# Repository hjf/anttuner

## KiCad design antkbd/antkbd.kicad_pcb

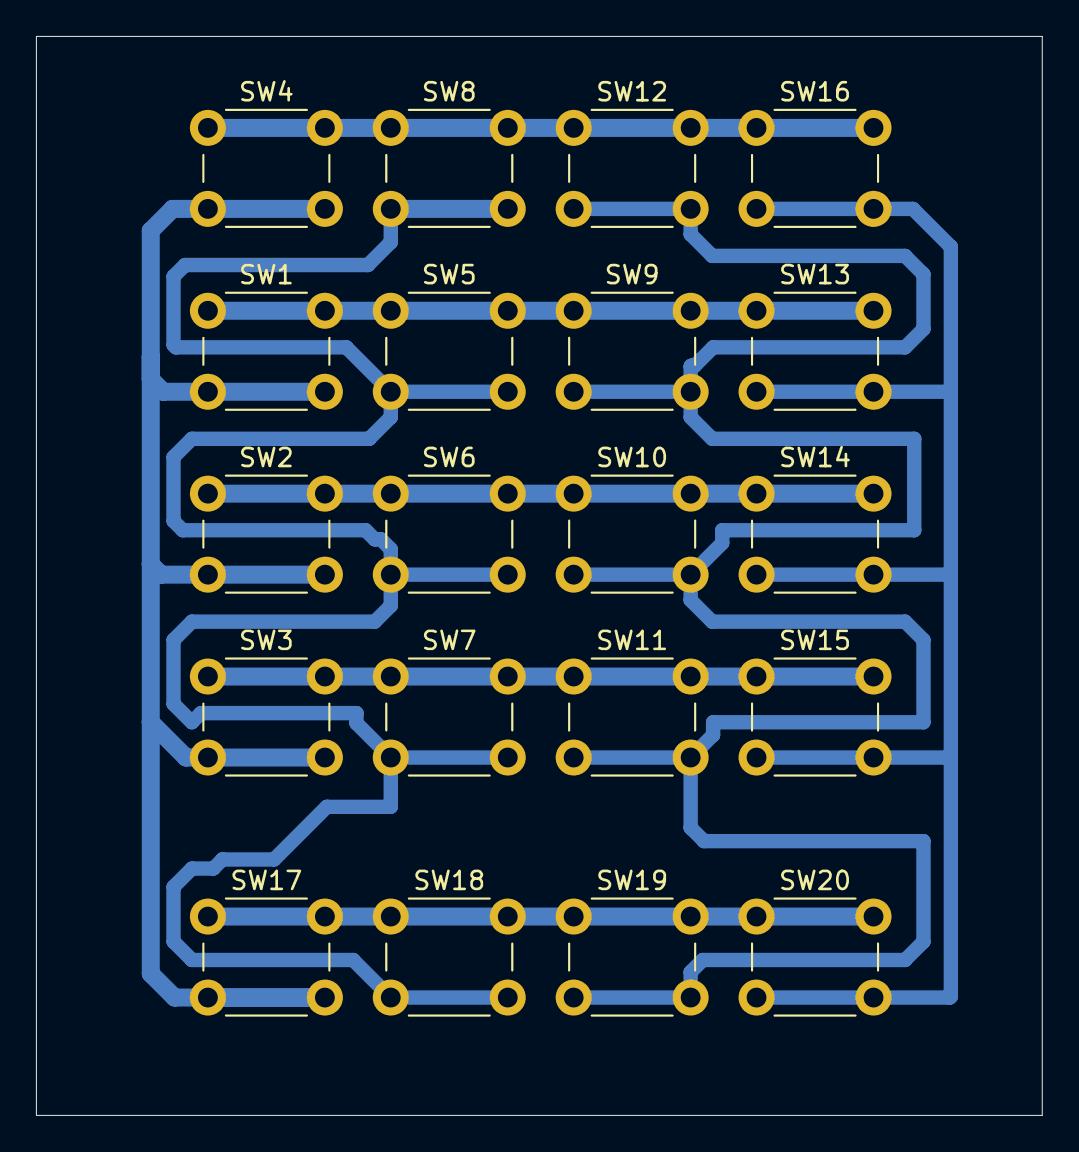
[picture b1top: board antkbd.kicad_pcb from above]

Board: 2 copper layers, 55.9 x 59.9 mm, 20 parts (0 on the bottom side), 9 nets.

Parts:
SW1, SW2, SW3, SW4, SW5, SW6, SW7, SW8, SW9, SW10, SW11, SW12, SW13, SW14, SW15, SW16, SW17, SW18, SW19, SW20: SW_Push_45deg; SW_PUSH_6mm

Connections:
unnamed: SW1.1, SW5.1, SW9.1, SW13.1
unnamed: SW1.2, SW2.2, SW3.2, SW4.2, SW17.2
unnamed: SW2.1, SW6.1, SW10.1, SW14.1
unnamed: SW9.2, SW10.2, SW11.2, SW12.2, SW19.2
unnamed: SW3.1, SW7.1, SW11.1, SW15.1
unnamed: SW4.1, SW8.1, SW12.1, SW16.1
unnamed: SW13.2, SW14.2, SW15.2, SW16.2, SW20.2
unnamed: SW17.1, SW18.1, SW19.1, SW20.1
unnamed: SW5.2, SW6.2, SW7.2, SW8.2, SW18.2

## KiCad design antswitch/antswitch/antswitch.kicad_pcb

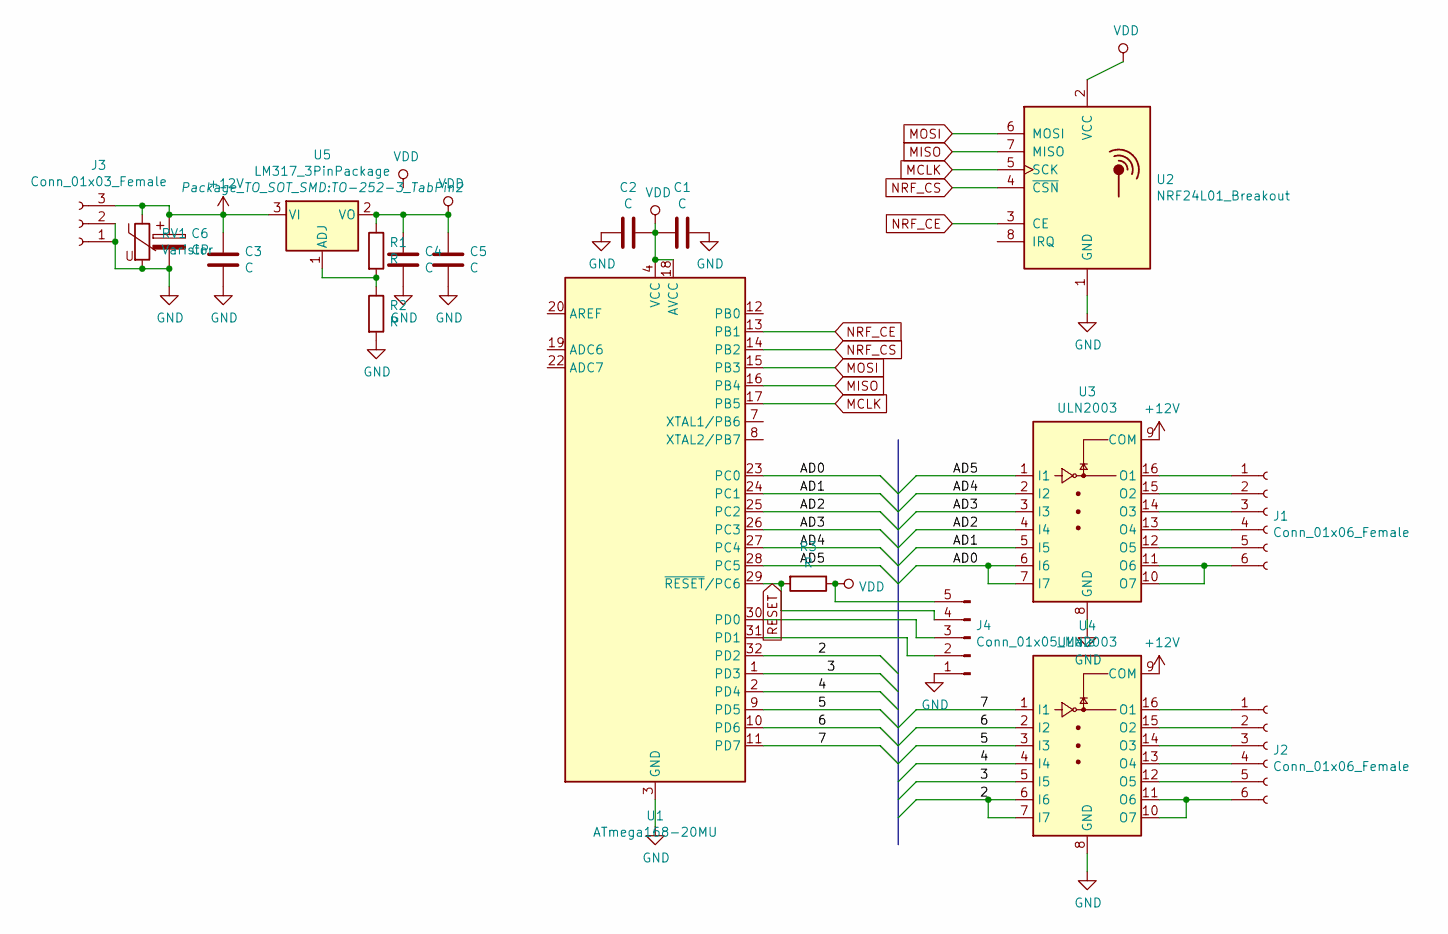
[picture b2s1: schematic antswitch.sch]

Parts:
C1, C2: C; C_0603_1608Metric
C3, C4, C5: C; C_0805_2012Metric_Pad1.15x1.40mm_HandSolder
C6: CP; CP_Elec_6.3x5.9
J1, J2: Conn_01x06_Female; PinHeader_1x06_P2.54mm_Vertical
J3: Conn_01x03_Female; PhoenixContact_MCV_1,5_3-G-5.08_1x03_P5.08mm_Vertical
J4: Conn_01x05_Male; PinHeader_1x05_P2.54mm_Vertical
R1, R2, R3: R; C_0805_2012Metric_Pad1.15x1.40mm_HandSolder
RV1: Varistor; RV_Disc_D15.5mm_W4mm_P7.5mm
U1: ATmega168-20MU; QFN-32-1EP_5x5mm_P0.5mm_EP3.1x3.1mm
U2: NRF24L01_Breakout; nRF24L01_Breakout
U3, U4: ULN2003; DIP-16_W7.62mm_LongPads
U5: LM317_3PinPackage; TO-252-3_TabPin2

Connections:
+12V: C3.1, C6.1, J3.3, RV1.1, U3.9 (COM), U4.9 (COM), U5.3 (VI)
/2: U1.32 (PD2), U4.6 (I6), U4.7 (I7)
/3: U1.1 (PD3), U4.5 (I5)
/4: U1.2 (PD4), U4.4 (I4)
/5: U1.9 (PD5), U4.3 (I3)
/6: U1.10 (PD6), U4.2 (I2)
/7: U1.11 (PD7), U4.1 (I1)
/AD0: U1.23 (PC0), U3.6 (I6), U3.7 (I7)
/AD1: U1.24 (PC1), U3.5 (I5)
/AD2: U1.25 (PC2), U3.4 (I4)
/AD3: U1.26 (PC3), U3.3 (I3)
/AD4: U1.27 (PC4), U3.2 (I2)
/AD5: U1.28 (PC5), U3.1 (I1)
GND: C1.1, C2.1, C3.2, C4.2, C5.2, C6.2, J3.1, J3.2, J4.1, R2.2, RV1.2, U1.3 (GND), U1.5 (GND), U1.21 (GND), U1.33 (GND), U2.1 (GND), U3.8 (GND), U4.8 (GND)
MCLK: U1.17 (PB5), U2.5 (SCK)
MISO: U1.16 (PB4), U2.7 (MISO)
MOSI: U1.15 (PB3), U2.6 (MOSI)
NRF_CE: U1.13 (PB1), U2.3 (CE)
NRF_CS: U1.14 (PB2), U2.4 (~CSN)
unnamed: J1.1, U3.16 (O1)
unnamed: J1.2, U3.15 (O2)
unnamed: J1.3, U3.14 (O3)
unnamed: J1.4, U3.13 (O4)
unnamed: J1.5, U3.12 (O5)
unnamed: J1.6, U3.10 (O7), U3.11 (O6)
unnamed: J2.1, U4.16 (O1)
unnamed: J2.2, U4.15 (O2)
unnamed: J2.3, U4.14 (O3)
unnamed: J2.4, U4.13 (O4)
unnamed: J2.5, U4.12 (O5)
unnamed: J2.6, U4.10 (O7), U4.11 (O6)
unnamed: J4.2, U1.31 (PD1)
unnamed: J4.3, U1.30 (PD0)
unnamed: R1.2, R2.1, U5.1 (ADJ)
RESET: J4.4, R3.2, U1.29 (~RESET~/PC6)
VDD: C1.2, C2.2, C4.1, C5.1, J4.5, R1.1, R3.1, U1.4 (VCC), U1.6 (VCC), U1.18 (AVCC), U2.2 (VCC), U5.2 (VO)

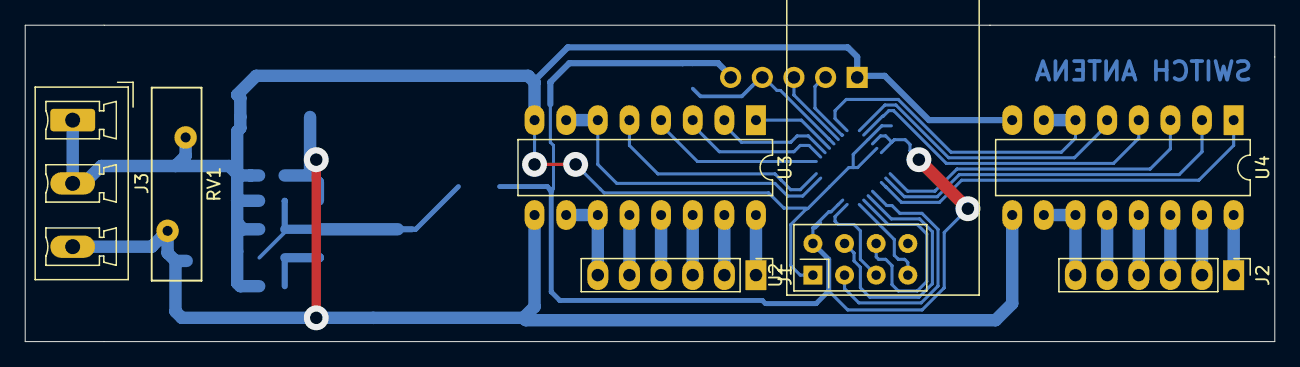
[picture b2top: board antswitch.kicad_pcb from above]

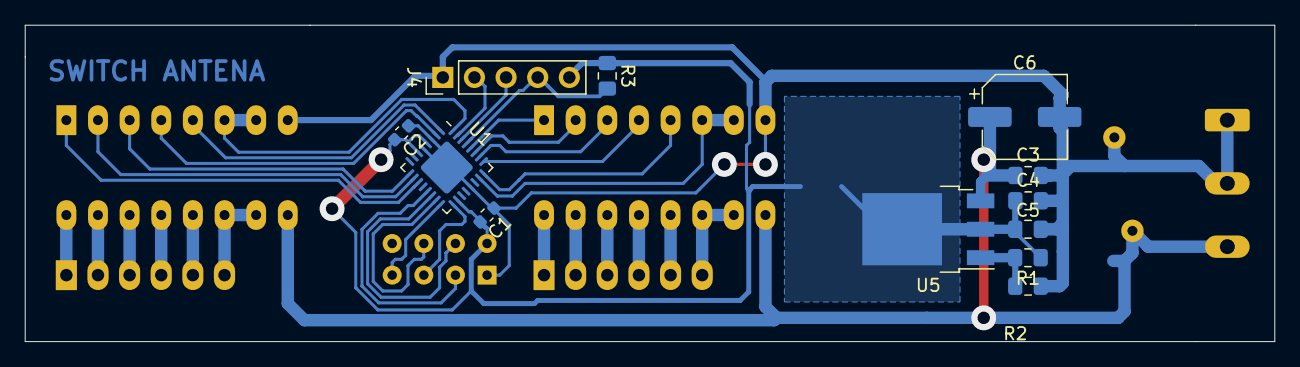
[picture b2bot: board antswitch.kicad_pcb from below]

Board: 2 copper layers, 100.3 x 25.4 mm, 19 parts (12 on the bottom side), 36 nets.

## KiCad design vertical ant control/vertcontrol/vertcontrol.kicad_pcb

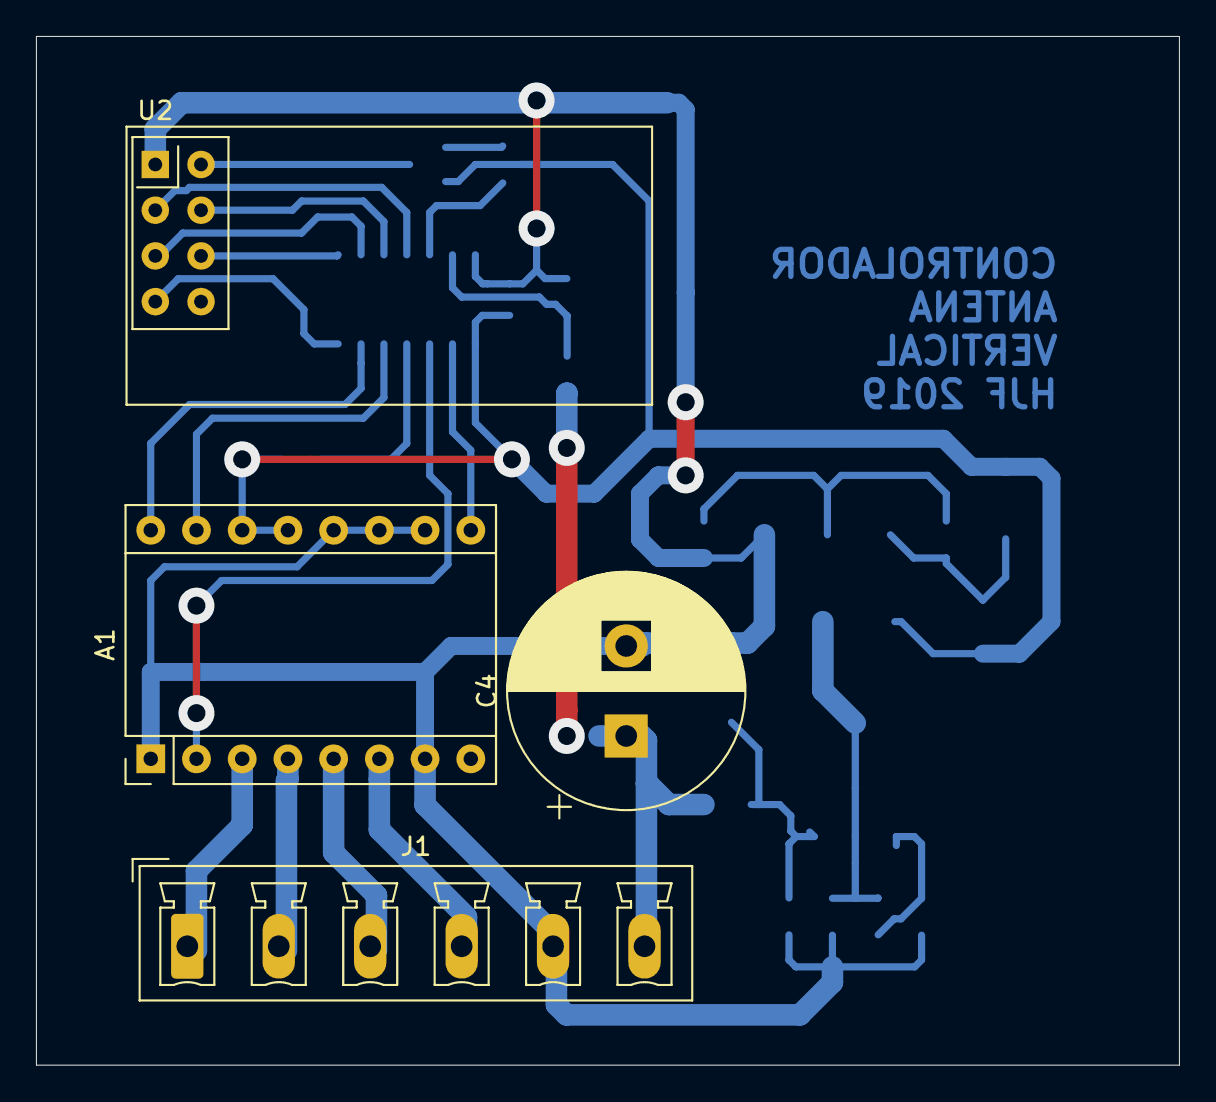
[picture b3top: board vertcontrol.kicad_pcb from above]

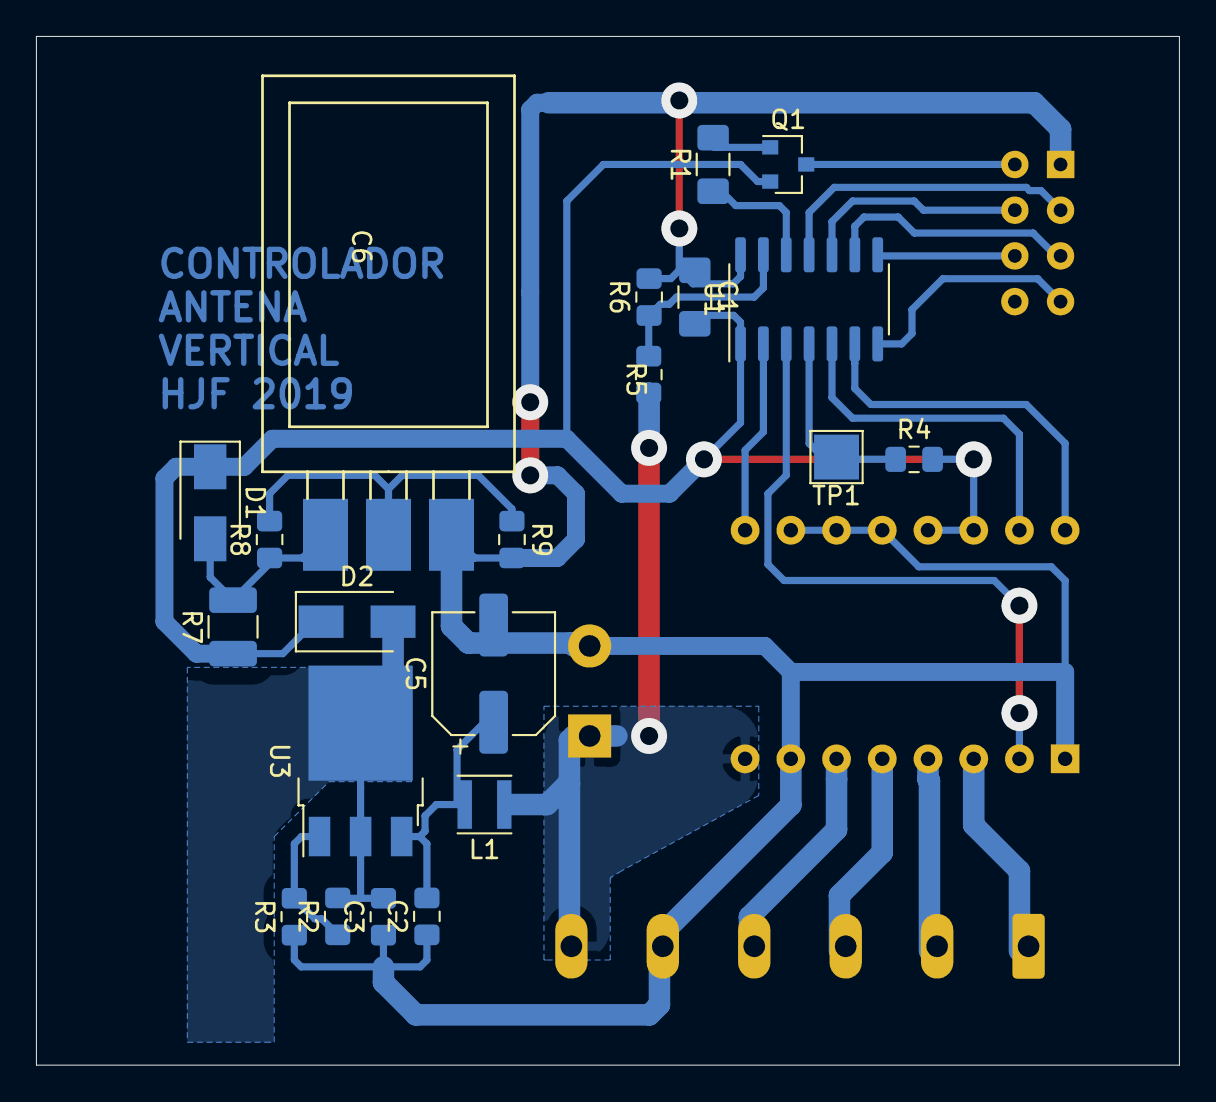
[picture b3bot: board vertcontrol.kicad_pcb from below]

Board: 2 copper layers, 63.5 x 57.2 mm, 25 parts (21 on the bottom side), 26 nets.

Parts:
A1: Pololu_Breakout_DRV8825; Pololu_Breakout-16_15.2x20.3mm
C1: 100n; C_1206_3216Metric_Pad1.42x1.75mm_HandSolder
C2, C3: 100n; C_0805_2012Metric_Pad1.15x1.40mm_HandSolder
C4: CP; CP_Radial_D13.0mm_P5.00mm
C5: CP; CP_Elec_6.3x5.8
C6: CAPACITOR3PIN; MURATA_SUPERCAP
D1, D2: D_Schottky; D_SMA
J1: Conn_01x06; PhoenixContact_MCV_1,5_6-G-5.08_1x06_P5.08mm_Vertical
L1: L; L_Taiyo-Yuden_MD-3030
Q1: Q_PMOS_GSD; SOT-23
R1: 1K; R_1206_3216Metric_Pad1.42x1.75mm_HandSolder
R2, R3, R4, R5, R6, R8, R9: 1K; R_0805_2012Metric_Pad1.15x1.40mm_HandSolder
R7: 1K; R_1210_3225Metric_Pad1.42x2.65mm_HandSolder
TP1: TestPoint; TestPoint_Pad_2.5x2.5mm
U1: ATtiny44-20SSU; SOIC-14_3.9x8.7mm_P1.27mm
U2: NRF24L01_Breakout; nRF24L01_Breakout
U3: LM317_3PinPackage; TO-252-3_TabPin2

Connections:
CE: U1.11, U2.3
CSN: U1.10, U2.4
GND: A1.1, A1.7, A1.10, A1.11, A1.12, C1.1, C2.1, C3.1, C4.2, C5.2, C6.1, J1.5, R3.1, R6.2, R9.2, U1.14, U2.1
MCLK: U1.9, U2.5
MISO: U1.7, U2.7
MOSI: U1.8, U2.6
MOT_DIR: A1.16, U1.6
MOT_EN: A1.9, U1.2
MOT_FLT: A1.2, U1.3
MOT_STEP: A1.15, U1.5
NRF_PWR: R1.1, U1.12
unnamed: A1.3, J1.1
unnamed: A1.4, J1.2
unnamed: A1.5, J1.3
unnamed: A1.6, J1.4
unnamed: C2.2, C5.1, L1.2, U3.3
unnamed: C3.2, D2.2, R2.2, U3.2
unnamed: C6.2, R8.2, R9.1
unnamed: C6.3, D1.2, R7.2, R8.1
unnamed: Q1.1, R1.2
unnamed: Q1.3, U2.2
unnamed: R2.1, R3.2, U3.1
unnamed: R4.1, TP1.1, U1.4
VDD: A1.13, A1.14, C1.2, D1.1, D2.1, Q1.2, R4.2, R7.1, U1.1
VMOT: A1.8, C4.1, J1.6, L1.1, R5.1
VSENSE: R5.2, R6.1, U1.13

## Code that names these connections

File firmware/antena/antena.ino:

#define DIR 7
#define STEP 8
#define EN 10
#define DRIVER_FAULT 9
#define NRF_CE 2
#define NRF_CS 3
#define NRF_PWR 1
#define VSENSE A0

#define MAX_STEPS 11860

//#define DEBUG

#ifdef DEBUG
#define MIN_US 50
#define MAX_US 1500
#else
#define MIN_US 100
#define MAX_US 1000
#endif

#include <avr/sleep.h>
#include <avr/wdt.h>

#include <RF24.h>
#include "tuner.h"

RF24 radio(NRF_CE, NRF_CS);

volatile bool interrupted;
bool step_state, await_adc;
int target_speed, current_speed, target_step, postdiv;
unsigned int wADC;
double t;
byte admux_copy;
struct antenna_response response;
byte stopcount;

void setup() {
#ifdef DEBUG
  Serial.begin(115200);
#endif
  pinMode(DIR, OUTPUT);
  pinMode(STEP, OUTPUT);
  pinMode(EN, OUTPUT);
  digitalWrite(EN, LOW);

  pinMode(DRIVER_FAULT, INPUT_PULLUP);
  pinMode(NRF_PWR, OUTPUT);
  digitalWrite(NRF_PWR, LOW);
  delay(100);

  initializeRadio();



  response.current_step = 0;

  postdiv = 0;
  admux_copy = ADMUX; //backup del registro como lo deja Arduino
  ADCSRA |= _BV(ADEN);  // enable the ADC
}

void loop() {

  byte pipeNo;
  struct antenna_request req;

  while ( radio.available(&pipeNo)) {

    radio.read( &req, sizeof(struct antenna_request) );

    radio.writeAckPayload(pipeNo, &response, sizeof(struct antenna_response) );

    if (req.command == NOOP) {
      continue;
    }

    if (req.command == STOP) {
      response.status = STOPPED;
    }

    if (req.command == SET_ZERO) {
      response.status = STOPPED;
      response.current_step == 0;
    }

    if (req.command == GOTO) {



      if (req.relative) {
        target_step += req.motion_value;
        target_speed = MAX_US;
      }      else {
        target_step = req.motion_value;
        target_speed = MAX_US;
      }

      if (target_step > MAX_STEPS)
        target_step = MAX_STEPS;
      if (target_step < 0)
        target_step = 0;

      if (target_step > response.current_step)
        response.status = GOING_UP;
      if (target_step < response.current_step)
        response.status = GOING_DOWN;


    }


    if (!await_adc) {
#ifdef DEBUG

      ADMUX = (_BV(REFS1) | _BV(REFS0) | _BV(MUX3));
#else
      ADMUX = 0b10100010;//(_BV(REFS1) | _BV(REFS0) | _BV(MUX3));
#endif

      ADCSRA |= _BV(ADSC);  // Start the ADC
      await_adc = true;
    }
  }

  if ((response.current_step <= 0  && response.status == GOING_DOWN) ||
      (response.current_step >= MAX_STEPS  && response.status == GOING_UP) ||
      (response.current_step <= target_step  && response.status == GOING_DOWN) ||
      (response.current_step >= target_step  && response.status == GOING_UP)
     )
  {
    response.status = STOPPED;
  }

  if (response.status == GOING_UP)
    digitalWrite(DIR, HIGH);
  if (response.status == GOING_DOWN)
    digitalWrite(DIR, LOW);



  if (response.status == GOING_UP || response.status == GOING_DOWN) {
    digitalWrite(EN, LOW);
    stopcount = 0;
  }
  else {
    if (stopcount == 255)
      digitalWrite(EN, HIGH);
    else
      stopcount++;
  }

  if (digitalRead(DRIVER_FAULT) == LOW)
    response.status = FAULT;

  if (await_adc && !bit_is_set(ADCSRA, ADSC)) {
    // Reading register "ADCW" takes care of how to read ADCL and ADCH.
    wADC = ADCW;

    // The offset of 324.31 could be wrong. It is just an indication.
    //t = (wADC - 324.31 ) / 1.22;
    t = wADC - (279);// + 100);// * 128;
    response.temperature = t;
    await_adc = false;
  } else {
    ADMUX = admux_copy;
    int rval = analogRead(A0);
    if (rval < 300) {
      goToSleep();

    }
  }

}

void goToSleep() {
  cli();

  TIMSK1 = (TIMSK1 & B11111110);// | 0x01;

  digitalWrite(NRF_PWR, HIGH); //apagar radio
  pinMode(0, INPUT);
  byte DDRA_copy = DDRA;
  byte DDRB_copy = DDRB;
  byte PORTA_copy = PORTA;
  byte PORTB_copy = PORTB;
  PORTA = 0x02; //NRF_PWR en HIGH
  PORTB = 0x00; //MOTOR_EN en HIGH
  DDRA = 0xfe; //todo out menos SENSE
  DDRB = 0xf8; //todo out menos FAULT

  ADCSRA &= ~ bit(ADEN); //apagar ADC
  PRR = 0xff; //maximo ahorro de energia
  MCUCR |= _BV(BODS); //apagar BOD en sleep

  GIMSK |= (1 << PCIE0);
  PCMSK0 = 1;
  wdt_disable();
  set_sleep_mode(SLEEP_MODE_PWR_DOWN);
  sleep_enable();
  sei();
  sleep_cpu();
  //-------a dormir
  GIMSK &= ~ (1 << PCIE0);
  PCMSK0 = 0;
  PRR = 0;
  ADCSRA |= _BV(ADEN); //encender ADC


  PORTA = PORTA_copy;
  PORTB = PORTB_copy;
  DDRA = DDRA_copy;
  DDRB = DDRB_copy;
  digitalWrite(NRF_PWR, LOW); //encender radio
  delay(100);
  initializeRadio();
  TIMSK1 = (TIMSK1 & B11111110) | 0x01;
}

ISR(PCINT0_vect)
{
  sleep_disable();
  //digitalWrite(NRF_PWR, LOW); //encender radio

}

ISR(EXT_INT0_vect)
{
  sleep_disable();
  //digitalWrite(NRF_PWR, LOW); //encender radio

}

void initializeRadio() {
  radio.begin();
  radio.enableAckPayload();                     // Allow optional ack payloads
  radio.enableDynamicPayloads();                // Ack payloads are dynamic payloads
  radio.setPALevel(RF24_PA_MAX);

  radio.openWritingPipe(addresses[ROLE_CONTROLLER]);
  radio.openReadingPipe(1, addresses[ROLE_ANTENNA]);
  radio.startListening();
  radio.writeAckPayload(1, &response, sizeof(struct antenna_response));

#ifdef DEBUG
  TIMSK2 = (TIMSK2 & B11111110) | 0x01;
  TCCR2B = (TCCR2B & B11111000) | 0x01;
#else
  TIMSK1 = (TIMSK1 & B11111110) | 0x01;
  TCCR1B = (TCCR1B & B11111000) | 0x01;
  TCNT1H = 0xff;
#endif
}

#ifdef DEBUG
ISR(TIMER2_OVF_vect) {
#else
ISR(TIM1_OVF_vect) {
  TCNT1 = 0xff00;
#endif



  if (response.status == STOPPED || response.status == FAULT) {
    current_speed = 0;
    step_state = 0;
    digitalWrite(STEP, step_state);
    return;
  }

  if (postdiv)
  {
    postdiv--;
    return;
  }

  if (abs(target_step - response.current_step) > 50) {
    if (current_speed < target_speed)
      current_speed += 8;
    if (current_speed > target_speed)
      current_speed = target_speed;
  } else {
    current_speed -= 8;
    if (current_speed < 1)
      current_speed = 1;
  }

  postdiv = MIN_US + (MAX_US - current_speed);

  step_state = !step_state;
  digitalWrite(STEP, step_state);

  if (step_state) {
    if (response.status == GOING_UP)
      response.current_step++;
    if (response.status == GOING_DOWN)
      response.current_step--;
  }

}

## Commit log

2019-10-17 Inicial
2019-10-20 switch control
2019-10-22 refactor controller
2019-10-24 controller modular
2019-10-24 tunable
2019-10-25 encoder
2020-02-09 serial proxy
2020-06-06 relay tuner
2020-06-15 conversion a platformio
2020-06-15 conversion platformio
2020-06-22 t/r switch
